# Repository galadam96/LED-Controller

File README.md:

# LED-Controller
A small project for learning to create complex MCU based RGB LED stick, that will change it's light according to it's orientation.

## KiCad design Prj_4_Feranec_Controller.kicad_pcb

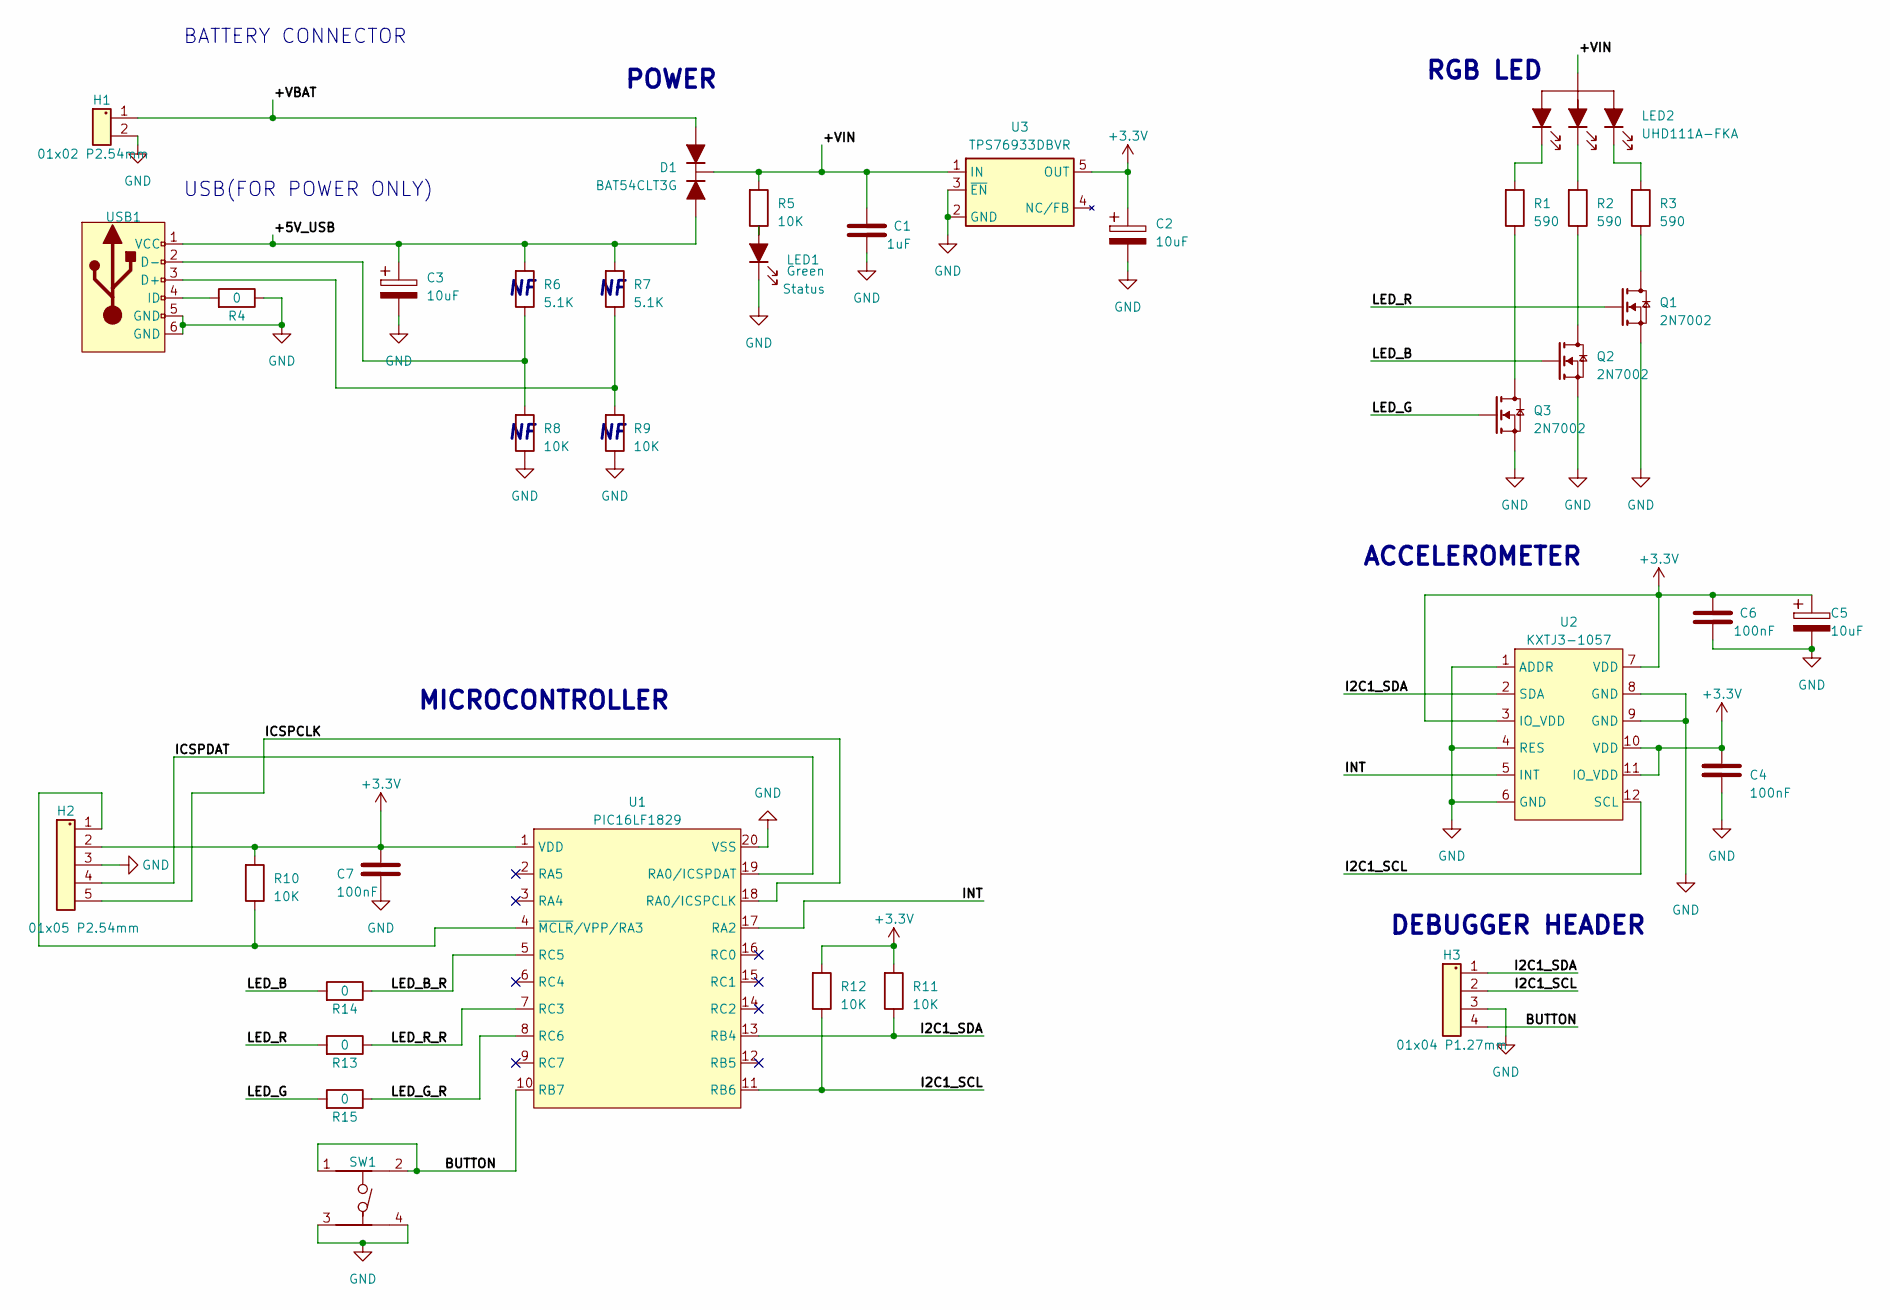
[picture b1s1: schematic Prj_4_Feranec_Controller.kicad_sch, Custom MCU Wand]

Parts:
C1: 1uF; C_0603
C2, C3, C5: 10uF; C_1206
C4, C6, C7: 100nF; C_0402
D1: BAT54CLT3G; D_SOT23_TO263
H1: 01x02 P2.54mm; Pin_Header_01x02_P2.54mm
H2: 01x05 P2.54mm; Pin_Header_01x05_P2.54mm
H3: 01x04 P1.27mm; Pin_Header_01x04_P1.27mm
LED1: Green; LED_0805_2012Metric
LED2: UHD111A-FKA; LED_RGB_404
Q1, Q2, Q3: 2N7002; D_SOT23_TO263
R1, R2, R3: 590; R_0402
R4, R13, R14, R15: 0; R_0402
R5, R8, R9, R10, R11, R12: 10K; R_0402
R6, R7: 5.1K; R_0402
SW1: SW_6x6
U1: PIC16LF1829; SSOP-20_5.3x7.2mm_P0.65mm
U2: KXTJ3-1057; LGA-12_2x2mm_P0.5mm
U3: TPS76933DBVR; SOT-23-5_HandSoldering
USB1: Custom_USB_Micro-B_Amphenol_10118194_Horizontal

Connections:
+3.3V: C2.1, C4.2, C5.1, C6.1, C7.2, H2.2, R10.1, R11.1, R12.1, U1.1 (VDD), U2.3 (IO_VDD), U2.7 (VDD), U2.10 (VDD), U2.11 (IO_VDD), U3.5 (OUT)
/+5V_USB: C3.1, D1.2, R6.1, R7.1, USB1.1 (VCC)
/+VBAT: D1.1, H1.1
/+VIN: C1.1, D1.3, LED2.4 (Anode), R5.1, U3.1 (IN)
/BUTTON: H3.4 (Pin_2), SW1.1, SW1.2, U1.10 (RB7)
/I2C1_SCL: H3.2, R12.2, U1.11 (RB6), U2.12 (SCL)
/I2C1_SDA: H3.1, R11.2, U1.13 (RB4), U2.2 (SDA)
/ICSPCLK: H2.5 (Pin_2), U1.18 (RA0/ICSPCLK)
/ICSPDAT: H2.4 (Pin_2), U1.19 (RA0/ICSPDAT)
/INT: U1.17 (RA2), U2.5 (INT)
/LED_B: Q2.1 (G), R14.1
/LED_B_R: R14.2, U1.5 (RC5)
/LED_G: Q3.1 (G), R15.1
/LED_G_R: R15.2, U1.8 (RC6)
/LED_R: Q1.1 (G), R13.1
/LED_R_R: R13.2, U1.7 (RC3)
GND: C1.2, C2.2, C3.2, C4.1, C5.2, C6.2, C7.1, H1.2, H2.3 (Pin_2), H3.3 (Pin_2), LED1.2, Q1.2 (S), Q2.2 (S), Q3.2 (S), R4.2, R8.2, R9.2, SW1.3, SW1.4, U1.20 (VSS), U2.1 (ADDR), U2.4 (RES), U2.6 (GND), U2.8 (GND), U2.9 (GND), U3.2 (GND), U3.3 (~EN), USB1.5 (GND), USB1.6 (GND)
unnamed: H2.1, R10.2, U1.4 (~MCLR/VPP/RA3)
unnamed: LED1.1, R5.2
unnamed: LED2.1 (B), R1.1
unnamed: LED2.2 (G), R2.1
unnamed: LED2.3 (R), R3.1
unnamed: Q1.3 (D), R3.2
unnamed: Q2.3 (D), R2.2
unnamed: Q3.3 (D), R1.2
unnamed: R7.2, R9.1, USB1.3 (D+)
unnamed: R6.2, R8.1, USB1.2 (D-)
unnamed: R4.1, USB1.4 (ID)

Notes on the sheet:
BATTERY CONNECTOR
ACCELEROMETER
RGB LED
USB(FOR POWER ONLY)
POWER
DEBUGGER HEADER
MICROCONTROLLER

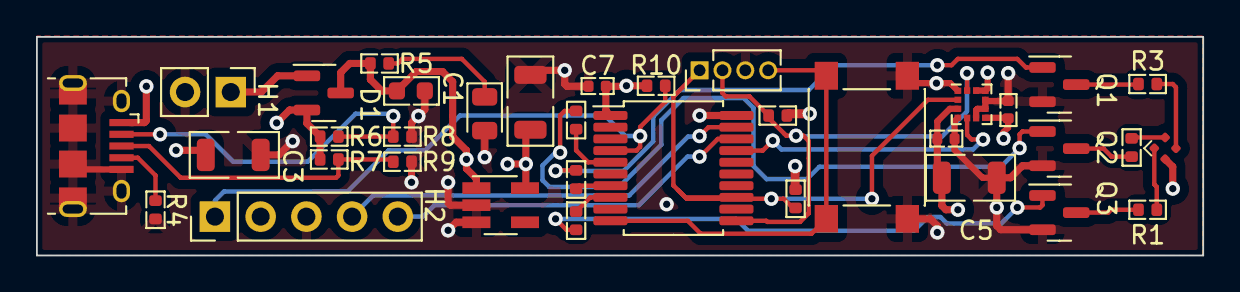
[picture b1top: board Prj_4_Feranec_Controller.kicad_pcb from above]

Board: 4 copper layers, 64.8 x 12.1 mm, 36 parts (0 on the bottom side), 28 nets.

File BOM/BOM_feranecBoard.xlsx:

| Component List |  |  |  | Bill of Material
 | Project: | Custom MCU Wand |  | Contact:
 |  |  |  | Adam Gal
 |  |  |  | galadam96@gmail.com
# | Category | Manufacturer | MPN | CasePackage | Description | Quantity | Designator | Footprint | Comment | Price HUF | Sum Price HUF | Price | Datasheet
1 | Optoelectronics | CreeLED, Inc. | UHD111A-FKA | 0404 | LED RGB 0404 SMD | 1 | LED2 |  | Min 580Ohm resistor | 14.82 | 14.82 |  | https://downloads.cree-led.com/files/ds/h/HB-UHD111A-FKA.pdf
2 | Resistors | YAGEO | RC0402FR-07590RL | 0402 | RES 590 OHM 1% 1/16W 0402 | 3 | R1,R2,R3 |  | Can be other manufacturer | 3.12 | 9.36 |  | https://www.yageo.com/upload/media/product/productsearch/dat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
3 | Accelerometers | Kionix Inc. | KXTJ3-1057 | LGA-12 | Accelerometer X, Y, Z Axis ±2g, 4g, 8g, 16g 800Hz 12-LGA (2x2) | 1 | U2 |  |  | 627.9 | 627.9 |  | https://kionixfs.azureedge.net/en/datasheet/KXTJ3-1057-Speci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
4 | Tactile Switches | C&K | PTS645SL43SMTR92 LFS | 6x6mm SMD | Tactile Switch SPST-NO Top Actuated Surface Mount | 1 | SW1 |  | Can be other manufacturer | 58.89 | 58.89 |  | https://www.ckswitches.com/media/1471/pts645.pdf
5 | Microcontrollers | Microchip Technology | PIC16LF1829-I/SS-ND | 20-SSOP | IC MCU 8BIT 14KB FLASH 20SSOP | 1 | U1 |  |  | 686.4 | 686.4 |  | https://ww1.microchip.com/downloads/aemDocuments/documents/O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
6 | Linear, Low Drop Out (LDO) Regulators | Texas Instruments | TPS76933DBVR | SOT-23-5 | IC REG LINEAR 3.3V 100MA SOT23-5 | 1 | U3 |  |  | 292.89 | 292.89 |  | https://www.ti.com/general/docs/suppproductinfo.tsp?distId=1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
7 | Capacitors | KYOCERA AVX | TAJA106K016RNJV | 1206 | CAP TANT 10UF 10% 16V 1206 | 3 | C2,C3,C5 |  | Can be other manufacturer | 63.96 | 191.88 |  | https://datasheets.kyocera-avx.com/TAJ.pdf
8 | Connectors | Adam Tech | PH1-02-UA | - | CONN HEADER VERT 2POS 2.54MM | 1 | H1 |  | Not populated | 177.84 | 177.84 |  | https://app.adam-tech.com/products/download/data_sheet/20160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
9 | Connectors | Amphenol ICC (FCI) | 10118194-0011LF | - | CONN RCPT USB2.0 MICRO B SMD R/A | 1 | USB1 |  |  | 0 | 0 |  | https://cdn.amphenol-cs.com/media/wysiwyg/files/drawing/1011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
10 | Resistors | Bourns Inc. | CR0402-FX-1002GLF | 0402 | RES SMD 10K OHM 1% 1/16W 0402 | 6 | R5,R8,R9,R10,R11,R12 |  | Can be other manufacturer | 2.73 | 16.38 |  | https://www.bourns.com/docs/product-datasheets/cr.pdf?sfvrsn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
11 | Resistors | Bourns Inc. | CR0402-JW-512GLF | 0402 | RES SMD 5.1K OHM 5% 1/16W 0402 | 2 | R6,R7 |  | Can be other manufacturer | 1.56 | 3.12 |  | https://www.bourns.com/docs/product-datasheets/cr.pdf?sfvrsn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
12 | Resistors | YAGEO | RC0402JR-070RL | 0402 | RES 0 OHM JUMPER 1/16W 0402 | 4 | R4,R13,R14,R15 |  | Can be other manufacturer | 2.73 | 10.92 |  | https://www.yageo.com/upload/media/product/productsearch/dat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
13 | Diodes | onsemi | BAT54CLT3G | SOT-23-3 (TO-236) | DIODE ARR SCHOTT 30V 200MA SOT23 | 1 | D1 |  |  | 40.950000000000003 | 40.950000000000003 |  | https://www.onsemi.com/pdf/datasheet/bat54clt1-d.pdf
14 | Optoelectronics | Wurth Elektronik | 150080VS75000 | 0805 | Standard LEDs - SMD WL-SMCW SMDMono TpVw Waterclr 0805 BrtGrn | 1 | LED1 |  | Can be other manufacturer | 67.86 | 67.86 |  | https://www.we-online.com/components/products/datasheet/1500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
15 | Transistors | Diotec Semiconductor | 2N7002 | SOT-23-3 (TO-236) | N-Channel 60 V 280mA (Ta) 350mW (Ta) Surface Mount SOT-23-3 (TO-236) | 3 | Q1,Q2,Q3 |  | Can be other manufacturer | 60.45 | 181.35000000000002 |  | https://diotec.com/request/datasheet/2n7002.pdf
16 | Capacitors | Samsung Electro-Mechanics | CL10A105KA8NNNC | 0603 | CAP CER 1UF 25V X5R 0603 | 1 | C1 |  | Can be other manufacturer | 5.85 | 5.85 |  | https://mm.digikey.com/Volume0/opasdata/d220001/medias/docus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
17 | Capacitors | Samsung Electro-Mechanics | CL05A104KA5NNNC | 0402 | CAP CER 0.1UF 25V X5R 0402 | 3 | C4,C6,C7 |  | Can be other manufacturer | 1.95 | 5.85 |  | https://mm.digikey.com/Volume0/opasdata/d220001/medias/docus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
18 | Connectors | Adam Tech | PH1-05-UA | - | Connector Header Through Hole 5 position 0.100" (2.54mm) | 1 | H2 |  | Not populated | 0 | 0 |  | https://app.adam-tech.com/products/download/data_sheet/20160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
19 | Connectors | Adam Tech | HPH1-A-04-UA | - | Connector Header Through Hole 4 position 0.050" (1.27mm) | 1 | H3 |  | Not populated | 0 | 0 |  | https://app.adam-tech.com/products/download/data_sheet/19995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
Notes: | Please do not populate the H1,H2,H3 Please fill in the price column K in this s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 |  |  |  |  |  |  |  | Total: | 2392.2599999999998 | HUF/PCS | Mouser w/o shipping
 |  |  |  |  |  |  |  |  | Price for 1pcs

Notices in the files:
Prj_4_Feranec_Controller.kicad_pcb:
v1.0 (C) 2023
